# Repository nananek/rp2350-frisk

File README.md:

# pico2-compat — Pico 2 相当 + 3×USB Type-C + CH343P UART + PIO USB

Raspberry Pi Pico 2 相当の RP2350A ボードです。外形は
[nananek/serial-km-emulator](https://github.com/nananek/serial-km-emulator)
と同じ **57.6 × 31.4 mm（四隅 2 mm 45° カット）** で、旧型フリスクケース
と同じ外形寸法に収まります。

Pico 2 との違いは次のとおりです。

- Pico の micro-B を **USB Type-C** に変更（RP2350 のネイティブ USB）
- **GPIO 40 ピンを Pico と同一配置**（2.54 mm ピッチ、17.78 mm 列間）
- **BOOT と RUN の独立ボタン**
- **UART0 を CH343P 経由の Type-C** に接続（最大 6 Mbps）
- **PIO USB ホスト用 Type-C**（GP12 = D+、GP13 = D-）
- 3.3 V は AP2112K、RP2350 内蔵の 1.1 V レギュレータを使用

## 仕様

| 項目 | 内容 |
| --- | --- |
| 基板 | 57.6 × 31.4 mm、t1.6 mm、4 層、四隅 2 mm 45° カット |
| MCU | RP2350A（QFN-60、7 × 7 mm） |
| フラッシュ | W25Q32JVSSIQ（4 MB、SOIC-8 208 mil） |
| 水晶 | 12 MHz（ABM8-272-T3、3225） |
| レギュレータ | AP2112K-3.3（600 mA、VSYS 3.8〜5.5 V） |
| ネイティブ USB | Type-C、USB 2.0 Full Speed、27 Ω 直列、USBLC6 ESD |
| UART | CH343P、Type-C、UART0（GP0/GP1）、3.3 V I/O、最大 6 Mbps |
| PIO USB（ホスト） | Type-C、GP12 = D+、GP13 = D-、22 Ω 直列、CC 56 kΩ Rp、VBUS は J1 から |
| GPIO | Pico 互換 2×20（1〜20 ピン / 21〜40 ピン）、2.54 mm ピッチ、17.78 mm 列間 |
| ボタン | BOOT（QSPI_SS を 1 kΩ で GND）、RUN（1 kΩ 経由で GND） |
| デバッグ | J4 1×3 ピンヘッダ（SWCLK / GND / SWDIO、未実装） |
| 電源 | J1/J3 の VBUS を BAT54WS でダイオード OR → VSYS。J2 の VBUS は出力 |
| 実装 | 表面実装のみ（Type-C のシェル固定タブは THT） |

## Pico 互換ピン配置

基板を USB 側から見て、ピン 1 が USB 端の GP0 です。Pico と同じく、
1〜20 ピンが一方の列、21〜40 ピンがもう一方の列に並びます。
2.54 mm ピッチ、列間 17.78 mm（0.7 インチ）です。

| ピン | 名称 | ピン | 名称 | ピン | 名称 | ピン | 名称 |
| --- | --- | --- | --- | --- | --- | --- | --- |
| 1 | GP0 / UART0 TX | 11 | GP8 | 21 | GP16 | 31 | GP26 / ADC0 |
| 2 | GP1 / UART0 RX | 12 | GP9 | 22 | GP17 | 32 | GP27 / ADC1 |
| 3 | GND | 13 | GND | 23 | GND | 33 | GND |
| 4 | GP2 | 14 | GP10 | 24 | GP18 | 34 | GP28 / ADC2 |
| 5 | GP3 | 15 | GP11 | 25 | GP19 | 35 | ADC_VREF |
| 6 | GP4 | 16 | GP12 / PIO D+ | 26 | GP20 | 36 | 3V3 |
| 7 | GP5 | 17 | GP13 / PIO D- | 27 | GP21 | 37 | 3V3_EN |
| 8 | GND | 18 | GND | 28 | GND | 38 | GND |
| 9 | GP6 | 19 | GP14 | 29 | GP22 | 39 | VSYS |
| 10 | GP7 | 20 | GP15 | 30 | RUN | 40 | VBUS |

Pico 2 でヘッダに出ていない GP23〜GP25、GP29 は、本基板でもヘッダには
出していません。SWD は J4（未実装）に引き出しています。

## USB ポート

J1 / J3 は **デバイス側（CC に 5.1 kΩ の Rd）**、J2 は **ホスト側
（CC に 56 kΩ の Rp）** です。J2 の VBUS は J1 の VBUS から 0 Ω（R11）で
供給する出力です。J1 / J3 はホスト PC と C-to-C でも C-to-A でも接続でき
ます。J2 にはキーボードや USB メモリなどを接続できますが、PC や充電器は
接続しないでください。

### J1: ネイティブ USB（右小口）

RP2350 の USB_DP / USB_DM（ピン 52 / 51）を 27 Ω で J1 に接続しています。
USBLC6 で ESD 保護しています。Pico と同じく、このポートの VBUS は
ヘッダの 40 ピン（VBUS）にも出ています。

### J3: UART（下長辺・右側）

CH343P の UD+ / UD- を J3 に直結しています。CH343 のデータシートで
「UD+/UD- に直列抵抗を入れてはいけない」と指定されているため、直列抵抗は
ありません。CH343P の VIO は 3.3 V、VDD5 は VSYS（約 4.7 V）です。
UART 側は 3.3 V I/O なので、RP2350 とレベル変換なしで接続できます。

```
GP0 (TX, pin 1) ──→ CH343P RXD (pin 5)
GP1 (RX, pin 2) ←── CH343P TXD (pin 4)
```

CTS/RTS は未接続です。6 Mbps は芯線だけの短い配線で使えますが、
フロー制御が必要な用途では 2 Mbps 以下を推奨します。USB Full Speed
(12 Mbps) の実効帯域も考慮してください。

Linux では `/dev/ttyUSB0` として見えます。CH343P は WCH の VID/PID で
認識され、Linux の `ch341` ドライバで動作します。

### J2: PIO USB ホスト（下長辺・左側）

GP12 を D+、GP13 を D- にしています。22 Ω の直列抵抗と USBLC6 を実装し、
Type-C の CC は 56 kΩ の Rp（既定の USB 電流）で VBUS にプルアップして
います。このポートは **ホスト専用** で、J1（またはヘッダ 40 ピンの
VBUS）から 5 V が供給されているときだけ VBUS が出ます。Pico-PIO-USB の
ホスト機能を使う場合は
`pin_dp = 12`、`pinout = PIO_USB_PINOUT_DPDM`（D- = 13）に設定してください。
D+ / D- のプルダウンは RP2350 の内蔵抵抗を使います。

J2 は出力専用です。PC や充電器を接続しないでください。デバイス用途に
変更する場合は、R11（0 Ω）を外して D+ に 1.5 kΩ のプルアップを追加し、
CC の 56 kΩ を 5.1 kΩ の Rd に変更してください。

## 電源

J1 / J3 の VBUS を BAT54WS（D1 / D3）で OR して VSYS を作り、
AP2112K-3.3 で 3.3 V を作ります。基板は J1 / J3 のどちらからでも給電
できます。ただし J2 の VBUS は J1（ヘッダ 40 ピンの VBUS と同じ）から
取るので、J2 を使うときは J1 側に 5 V が必要です。

- VSYS: 3.8〜5.5 V（AP2112K のドロップアウトのため。USB 給電時は約 4.7 V）
- 3V3: 最大 600 mA（LDO の定格）
- RP2350 の 1.1 V は内蔵レギュレータ（VREG_VIN / VREG_LX / VREG_FB）と
  3.3 µH（L1）で生成。DVDD（ピン 6 / 23 / 39）は 1V1 に接続し、
  C11 / C12 / C30 でデカップリングします
- 3V3_EN（ヘッダ 37 ピン）は 100 kΩ で VSYS にプルアップ。GND に落とすと
  3.3 V が停止します
- VBUS（ヘッダ 40 ピン）は J1 の VBUS に直結
- J2 の VBUS は J1 の VBUS（ヘッダ 40 ピンと同じ）から R11（0 Ω）で供給
- VSYS（ヘッダ 39 ピン）はダイオード OR 後の共通 5 V

Pico の 3V3 ピン（36）は本基板では LDO 出力です。外部から 3V3 を
逆駆動しないでください。VSYS から給電する場合も、LDO の入力範囲
（3.8 V 以上）を守ってください。バッテリー直結（3.7 V 以下）では
3.3 V が低下します。

## BOOT / RUN

- **BOOT**: QSPI_SS とフラッシュ CS の間の 0 Ω（R14）の前から 1 kΩ（R12）で
  ボタンに引き出しています。BOOT を押したままリセットすると、RP2350 の
  USB ブートローダー（BOOTSEL）に入ります。
- **RUN**: RUN ピンを 1 kΩ（R13）経由で GND に落とします。

BOOT と RUN は独立したタクトスイッチ（TS-1187A、5.1 × 5.1 mm）です。

## 基板外形とケース

外形は serial-km-emulator と同一の 57.6 × 31.4 mm、四隅 2 mm 45° カット
です。配線とグラウンドの都合で 4 層にしています。旧型フリスクケースの内寸には収まりますが、コネクタの位置が違うため
ケースの開口を変更してください。

- J2 / J3（PIO USB / UART）: 下長辺に 2 個。開口は約 30 × 5 mm
- J1（ネイティブ USB）: 右小口に 1 個。開口は約 10 × 5 mm
- BOOT / RUN: 基板の表側、左右の端。ケースに穴を開けるか、蓋を外して押します

コネクタの口は基板端から約 1.5 mm 外に出ます。USB-C プラグの
オーバーモールドがケースに当たる場合は、開口の外側を面取りしてください。

## 部品表（JLCPCB）

`fab/bom_jlcpcb.csv` が JLCPCB 用 BOM、`fab/cpl_jlcpcb.csv` が CPL です。
主な部品は次のとおりです（2026-11 時点の JLCPCB 在庫確認済み）。

| 記号 | 値 | パッケージ | LCSC | 備考 |
| --- | --- | --- | --- | --- |
| U1 | RP2350A | QFN-60 7×7 | C42411118 | 拡張部品 |
| U2 | W25Q32JVSSIQ | SOIC-8 208 mil | C179173 | 4 MB |
| U3 | CH343P | QFN-16 3×3 | C2846043 | 6 Mbps、水晶不要 |
| U4 | AP2112K-3.3 | SOT-23-5 | C51118 | 600 mA LDO |
| J1〜J3 | TYPE-C-31-M-12 | USB-C 16P | C165948 | HRO |
| D1, D3 | BAT54WS | SOD-323 | C22629 | VBUS OR |
| D4〜D6 | USBLC6-2SC6 | SOT-23-6 | C7519 | ESD |
| Y1 | ABM8-272-T3 | 3225 4 pin | C20625731 | 12 MHz |
| L1 | 3.3 µH | 2016 | C42411119 | RP2350 1.1 V 用 |
| SW1, SW2 | TS-1187A-B-A-B | 5.1×5.1 mm | C318884 | BOOT / RUN |
| R1, R2, R5, R6 | 5.1 kΩ | 0603 | C23186 | CC（デバイス） |
| R3, R4 | 56 kΩ | 0603 | C23206 | CC（ホスト Rp） |
| R7, R8 | 27 Ω | 0603 | C25190 | ネイティブ USB |
| R9, R10 | 22 Ω | 0603 | C23345 | PIO USB |
| R11 | 0 Ω | 0603 | C21189 | PIO VBUS（J1 VBUS → J2） |
| R12, R13, R18〜R20 | 1 kΩ | 0603 | C21190 | BOOT/RUN/LED/水晶 |
| R14 | 0 Ω | 0603 | C21189 | QSPI_SS |
| R15 | 33 Ω | 0603 | C23140 | VREG_AVDD |
| R16 | 200 Ω | 0603 | C8218 | ADC_VREF |
| R17 | 100 kΩ | 0603 | C14675 | 3V3_EN |
| C1〜C3, C7, C9 | 10 µF | 0805 | C15850 | VBUS / VSYS / 3V3 |
| C11, C13, C30 | 4.7 µF | 0805 | C1779 | 1V1（C30 はピン 23 付近） / VREG_AVDD |
| C4〜C6, C8, C10, C12, C14〜C29 | 100 nF | 0603 | C14663 | デカップリング |
| C25, C26 | 15 pF | 0603 | C1644 | 水晶 |
| LED1, LED2 | KT-0603R | 0603 | C2286 | PWR / UART ACT |

J5A / J5B（Pico ヘッダ）と J4（SWD）は **未実装** です。BOM / CPL には
入りません。

## JLCPCB での発注

基板:

- 4 層、57.6 × 31.4 mm、t1.6 mm、FR-4、HASL、1 oz
- 内層: In1 = GND ベタ、In2 = 3V3 ベタ
- 最小配線幅/間隔 0.10/0.15 mm、ビア 0.5/0.3 mm
- 仕上げはお好みで（HASL / 鉛フリー HASL / ENIG）

実装:

- 表面のみ
- アップロードするファイル:
  - ガーバー: `fab/pico2-compat-gerbers.zip`
  - BOM: `fab/bom_jlcpcb.csv`
  - CPL: `fab/cpl_jlcpcb.csv`
- Type-C のシェル固定タブは THT 形状ですが、JLCPCB の SMT 実装部品として
  登録されています（C165948）。
- CPL の回転は KiCad → JLC の一般的な補正を入れてあります。必ず
  JLCPCB の実装プレビューで IC のピン 1 と Type-C の向きを確認してください。
- R3 / R4 の VBUS 側は 0603 パッド内のビア（0.5/0.3 mm）で VBUS_PIO に
  接続しています。量産時は via-in-pad のビア埋めを検討してください。
- QFN（RP2350A / CH343P）は拡張部品です。手半田する場合は、センターパッド
  へのプリフォーム半田またはホットエアを使ってください。

## 再生成

KiCad 10 の `kicad-cli` と Python の `pcbnew` を使います。Docker がある場合は
`scripts/kicad.sh` 経由で実行できます。

```sh
# 回路図と配置（配線は消えるので注意）
./scripts/kicad.sh python3 scripts/gen_sch.py
./scripts/kicad.sh python3 scripts/gen_pcb.py

# ガーバー、ドリル、BOM、CPL、PDF
./scripts/kicad.sh ./scripts/export_fab.sh
```

`pico2-compat.kicad_pcb` は `scripts/gen_pcb.py` が配置と外形を作り、
`scripts/route.sh` の Freerouting で配線を入れています。配置を変えた場合は
配線をやり直してください。`scripts/finish_pcb.py` が GND ベタを追加して
フィルし、最終基板を作ります。

```sh
./scripts/route.sh          # DSN 書き出し → Freerouting → SES 取り込み
./scripts/kicad.sh python3 scripts/finish_pcb.py
```

Freerouting は [`freerouting/freerouting`](https://github.com/freerouting/freerouting)
の CLI を使います。Java 21 以上が必要です。

## 検証

GitHub Actions（`.github/workflows/ci.yml`）で次を実行します。

- ERC: 0 件
- DRC: エラー 0 件（`--severity-error`）
- ガーバー、ドリル、BOM、CPL、PDF の生成
- 生成物のアップロード

シルクの文字高やシルクとパッドのクリアランスは警告として残る場合があります。
製造には影響しませんが、気になる場合はシルクを調整してください。

## 制限事項

- PIO USB（J2）はホスト専用です。VBUS は J1（またはヘッダ 40 ピン）から
  供給されるため、J1 側に 5 V がないと J2 のデバイスは動作しません。J2 から
  基板へ給電することはできません。
- CH343P の CTS/RTS は未接続です。
- 3.3 V は LDO のため、VSYS が 3.8 V を下回ると 3.3 V が低下します。
- Pico 2 の buck-boost のような広い VSYS 入力範囲ではありません。
- GP23〜GP25、GP29 はヘッダに出ていません（Pico と同じ）。
- SWD は J4 に引き出していますが、実装はしていません。
- ネイティブ USB の VBUS（ヘッダ 40 ピン）と VSYS（39 ピン）は Pico と
  同じ向きですが、3V3（36 ピン）を外部から逆駆動しないでください。

## ファイル構成

```
pico2-compat.kicad_pro / .kicad_sch / .kicad_pcb / .kicad_dru
lib/pico2.kicad_sym          回路図シンボル
lib/PICO2.pretty/            フットプリント
scripts/design.py            部品・ネットの単一ソース
scripts/gen_sch.py           回路図生成
scripts/gen_pcb.py           配置・外形生成
scripts/route.sh             Freerouting による配線
scripts/finish_pcb.py        GND ベタ追加・フィル
scripts/export_fab.sh        ガーバー/BOM/CPL/PDF 生成
scripts/make_jlc_files.py    JLCPCB BOM/CPL 変換
.github/workflows/ci.yml     CI
fab/                         発注用ファイル（生成物）
docs/                        基板画像・回路図 PDF
```

## ライセンス

MIT。基板の製造・実装は自己責任で行ってください。特に Type-C のシェル
固定タブ、USB の差し込み方向、ケースの開口寸法は、発注前に各自の環境で
確認してください。

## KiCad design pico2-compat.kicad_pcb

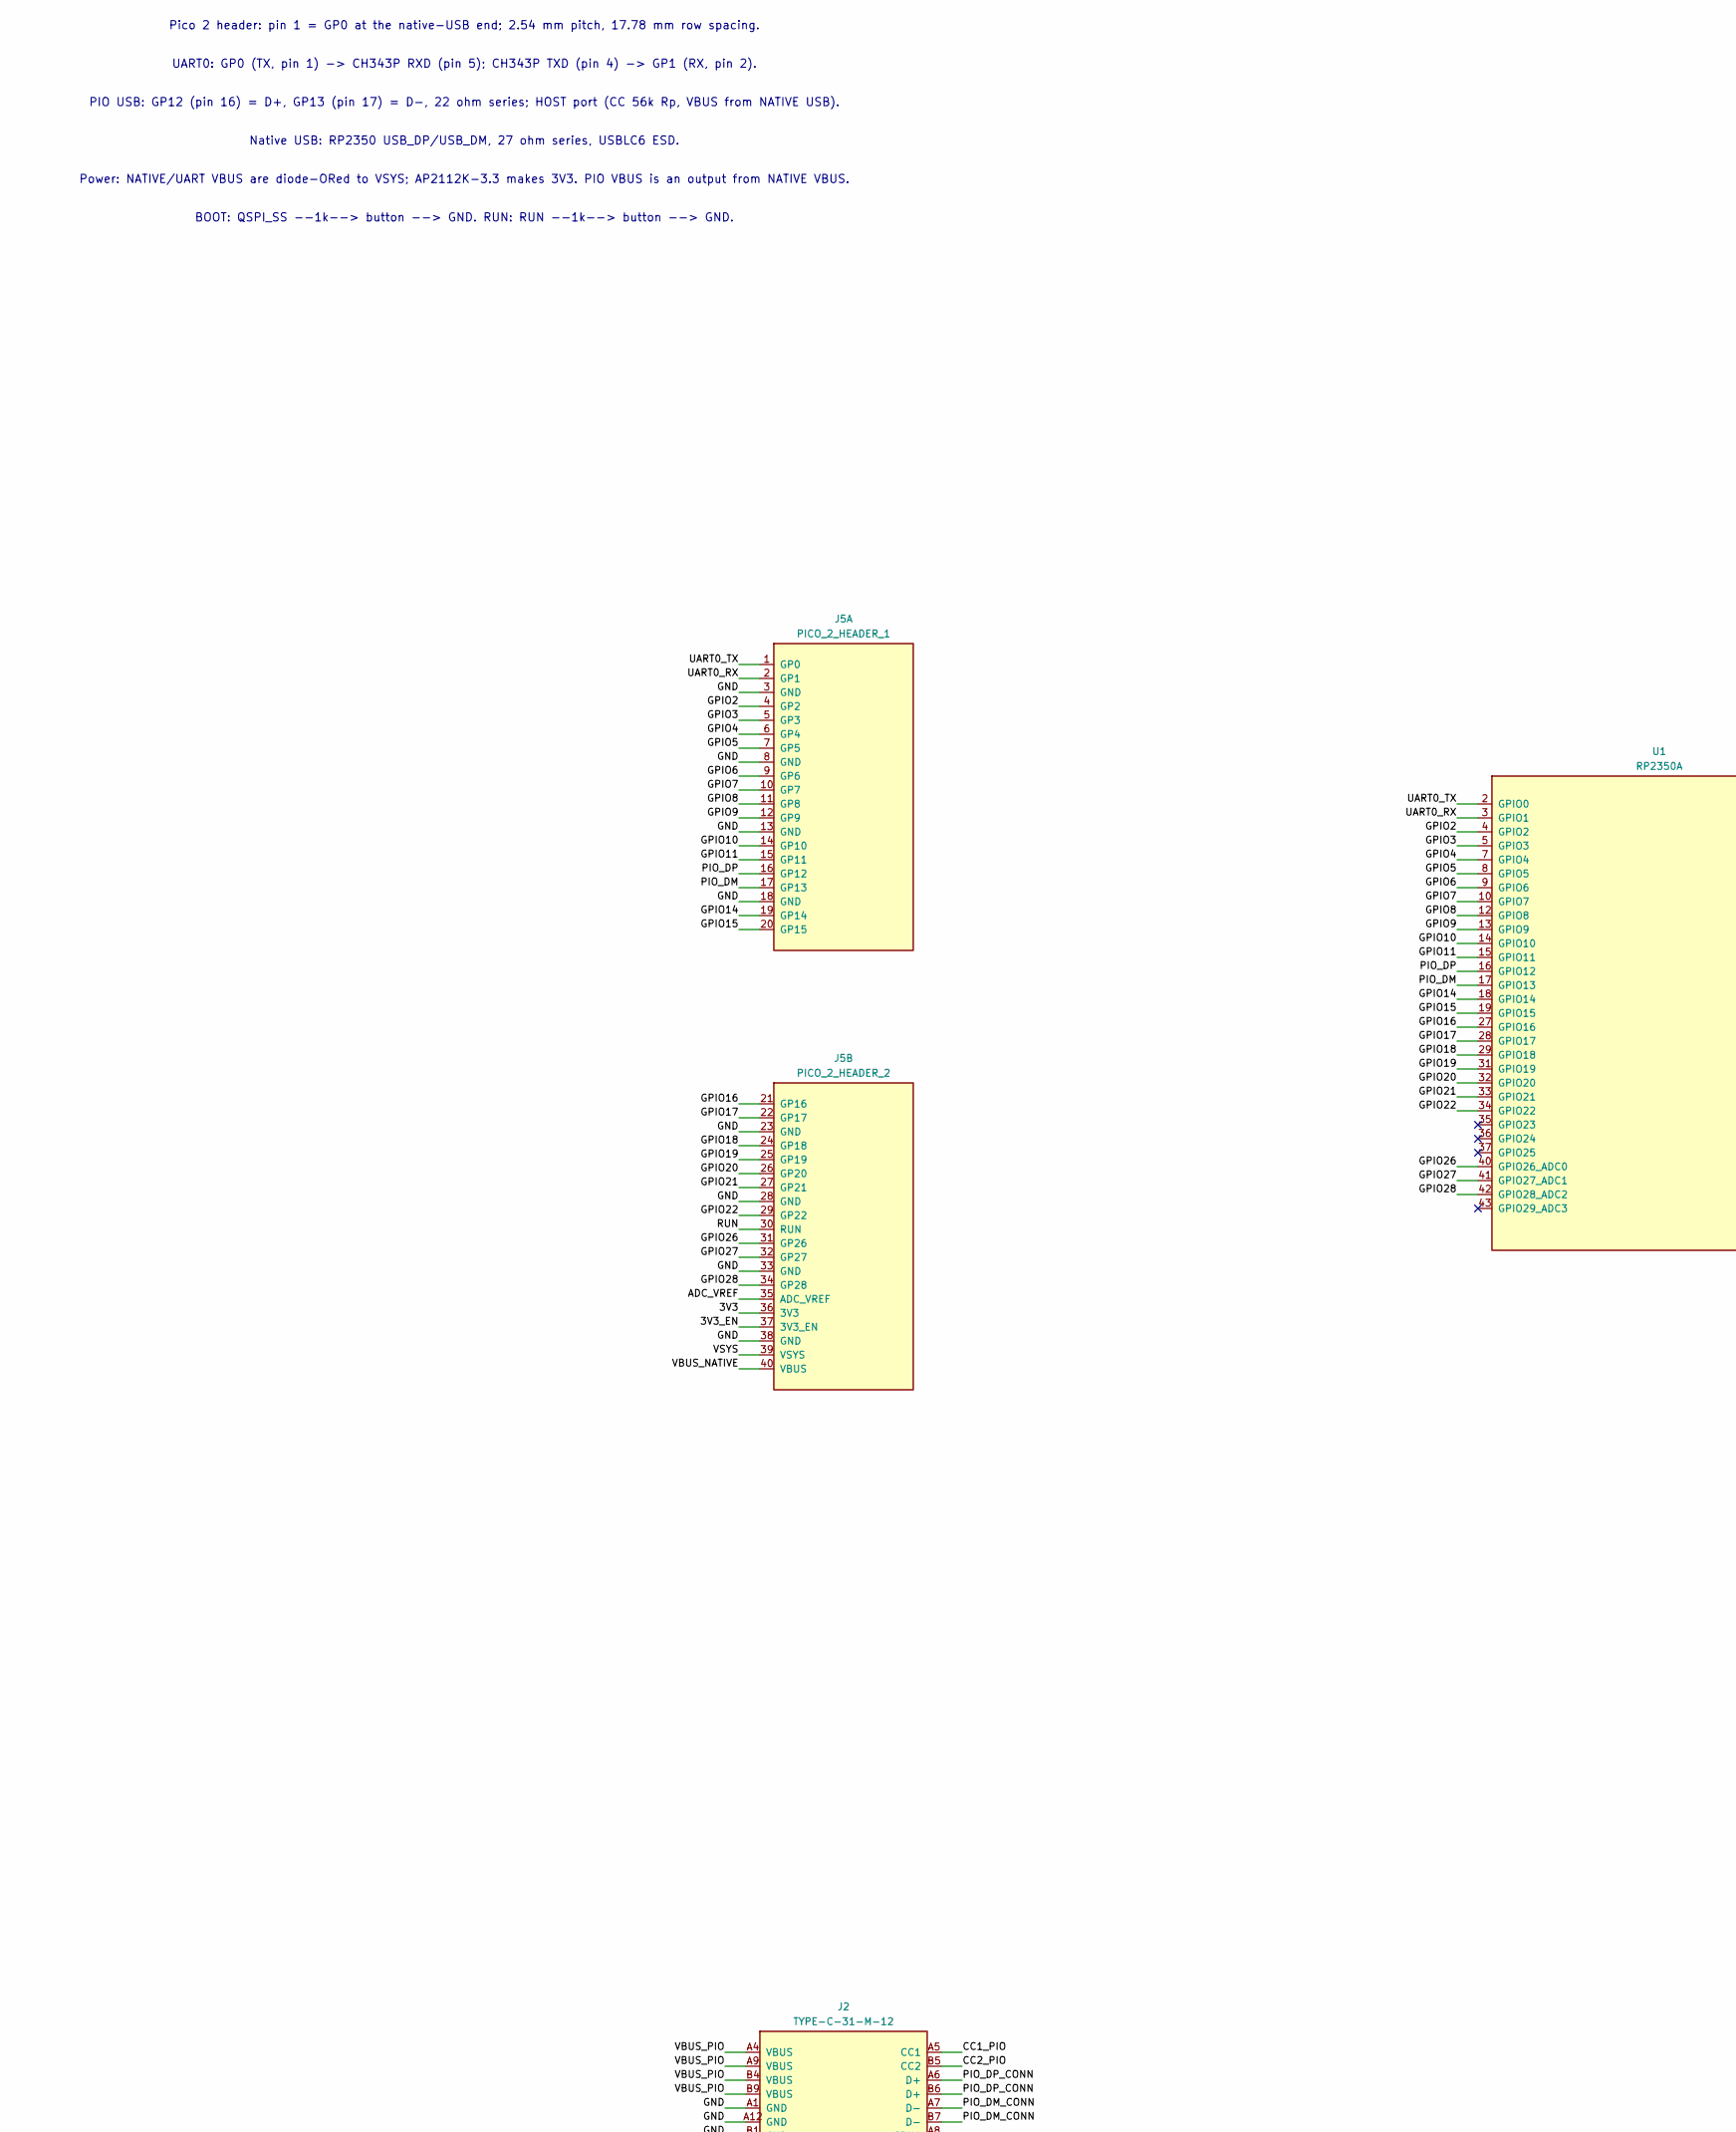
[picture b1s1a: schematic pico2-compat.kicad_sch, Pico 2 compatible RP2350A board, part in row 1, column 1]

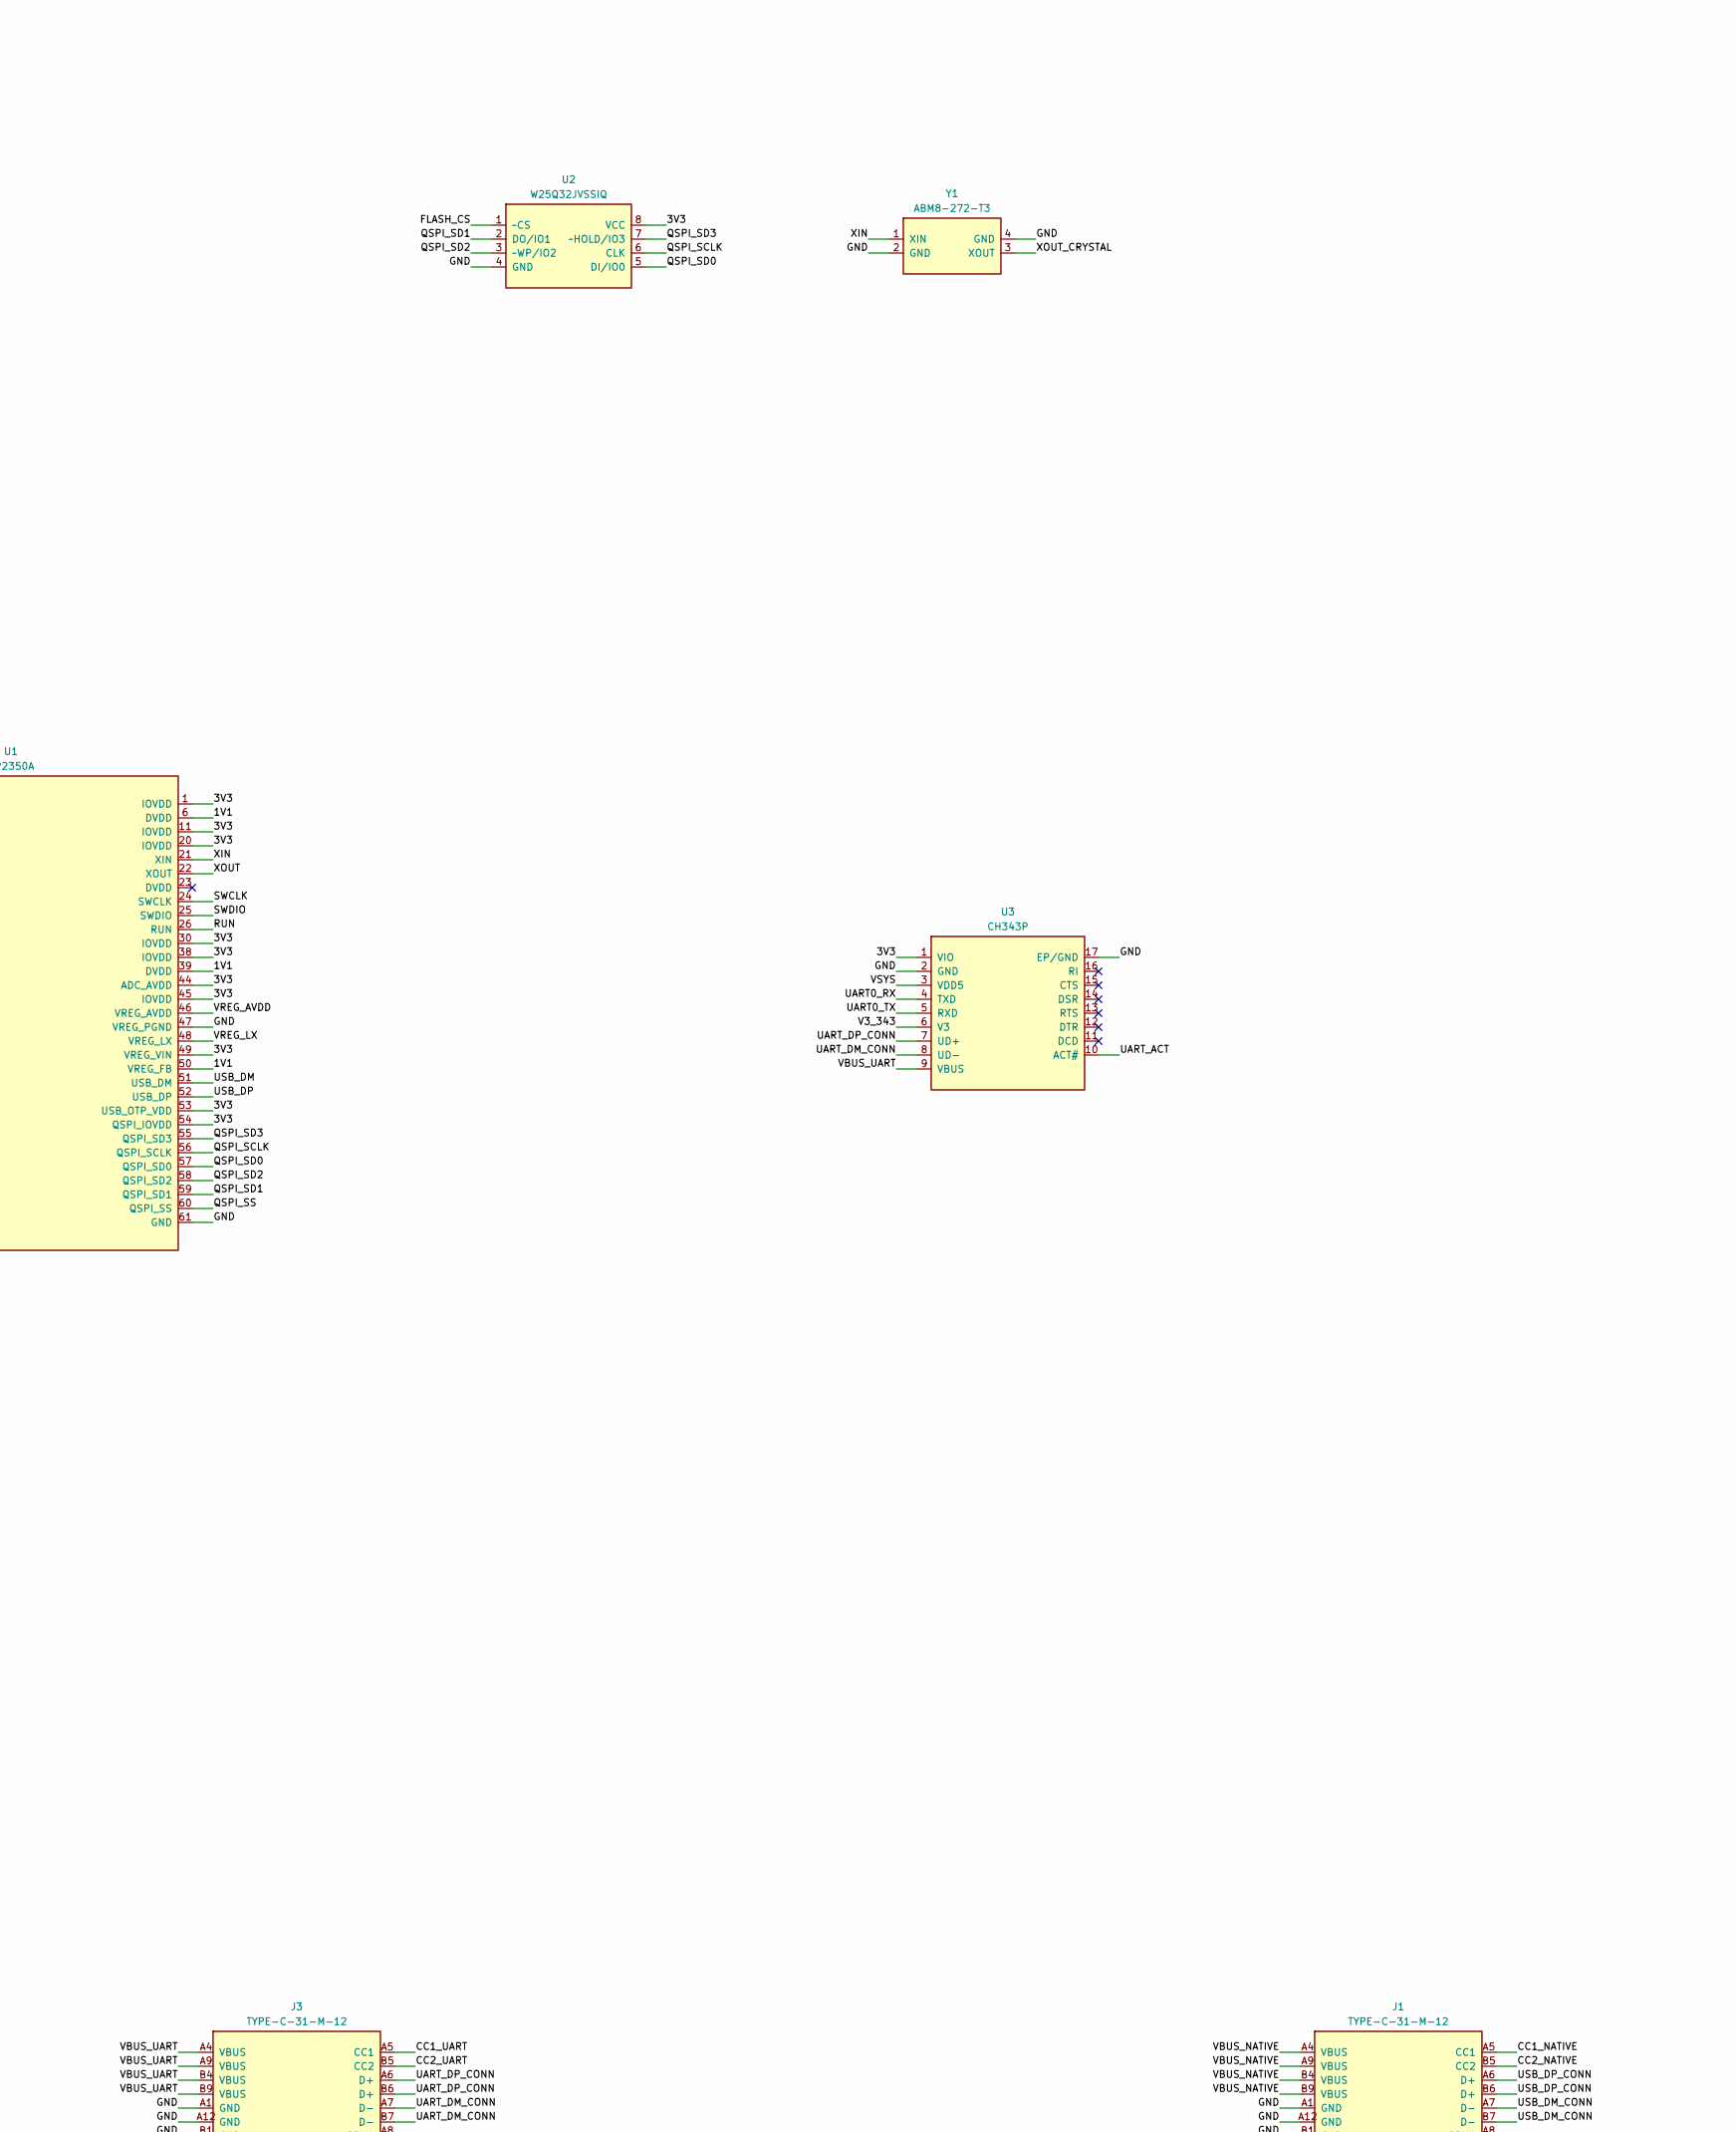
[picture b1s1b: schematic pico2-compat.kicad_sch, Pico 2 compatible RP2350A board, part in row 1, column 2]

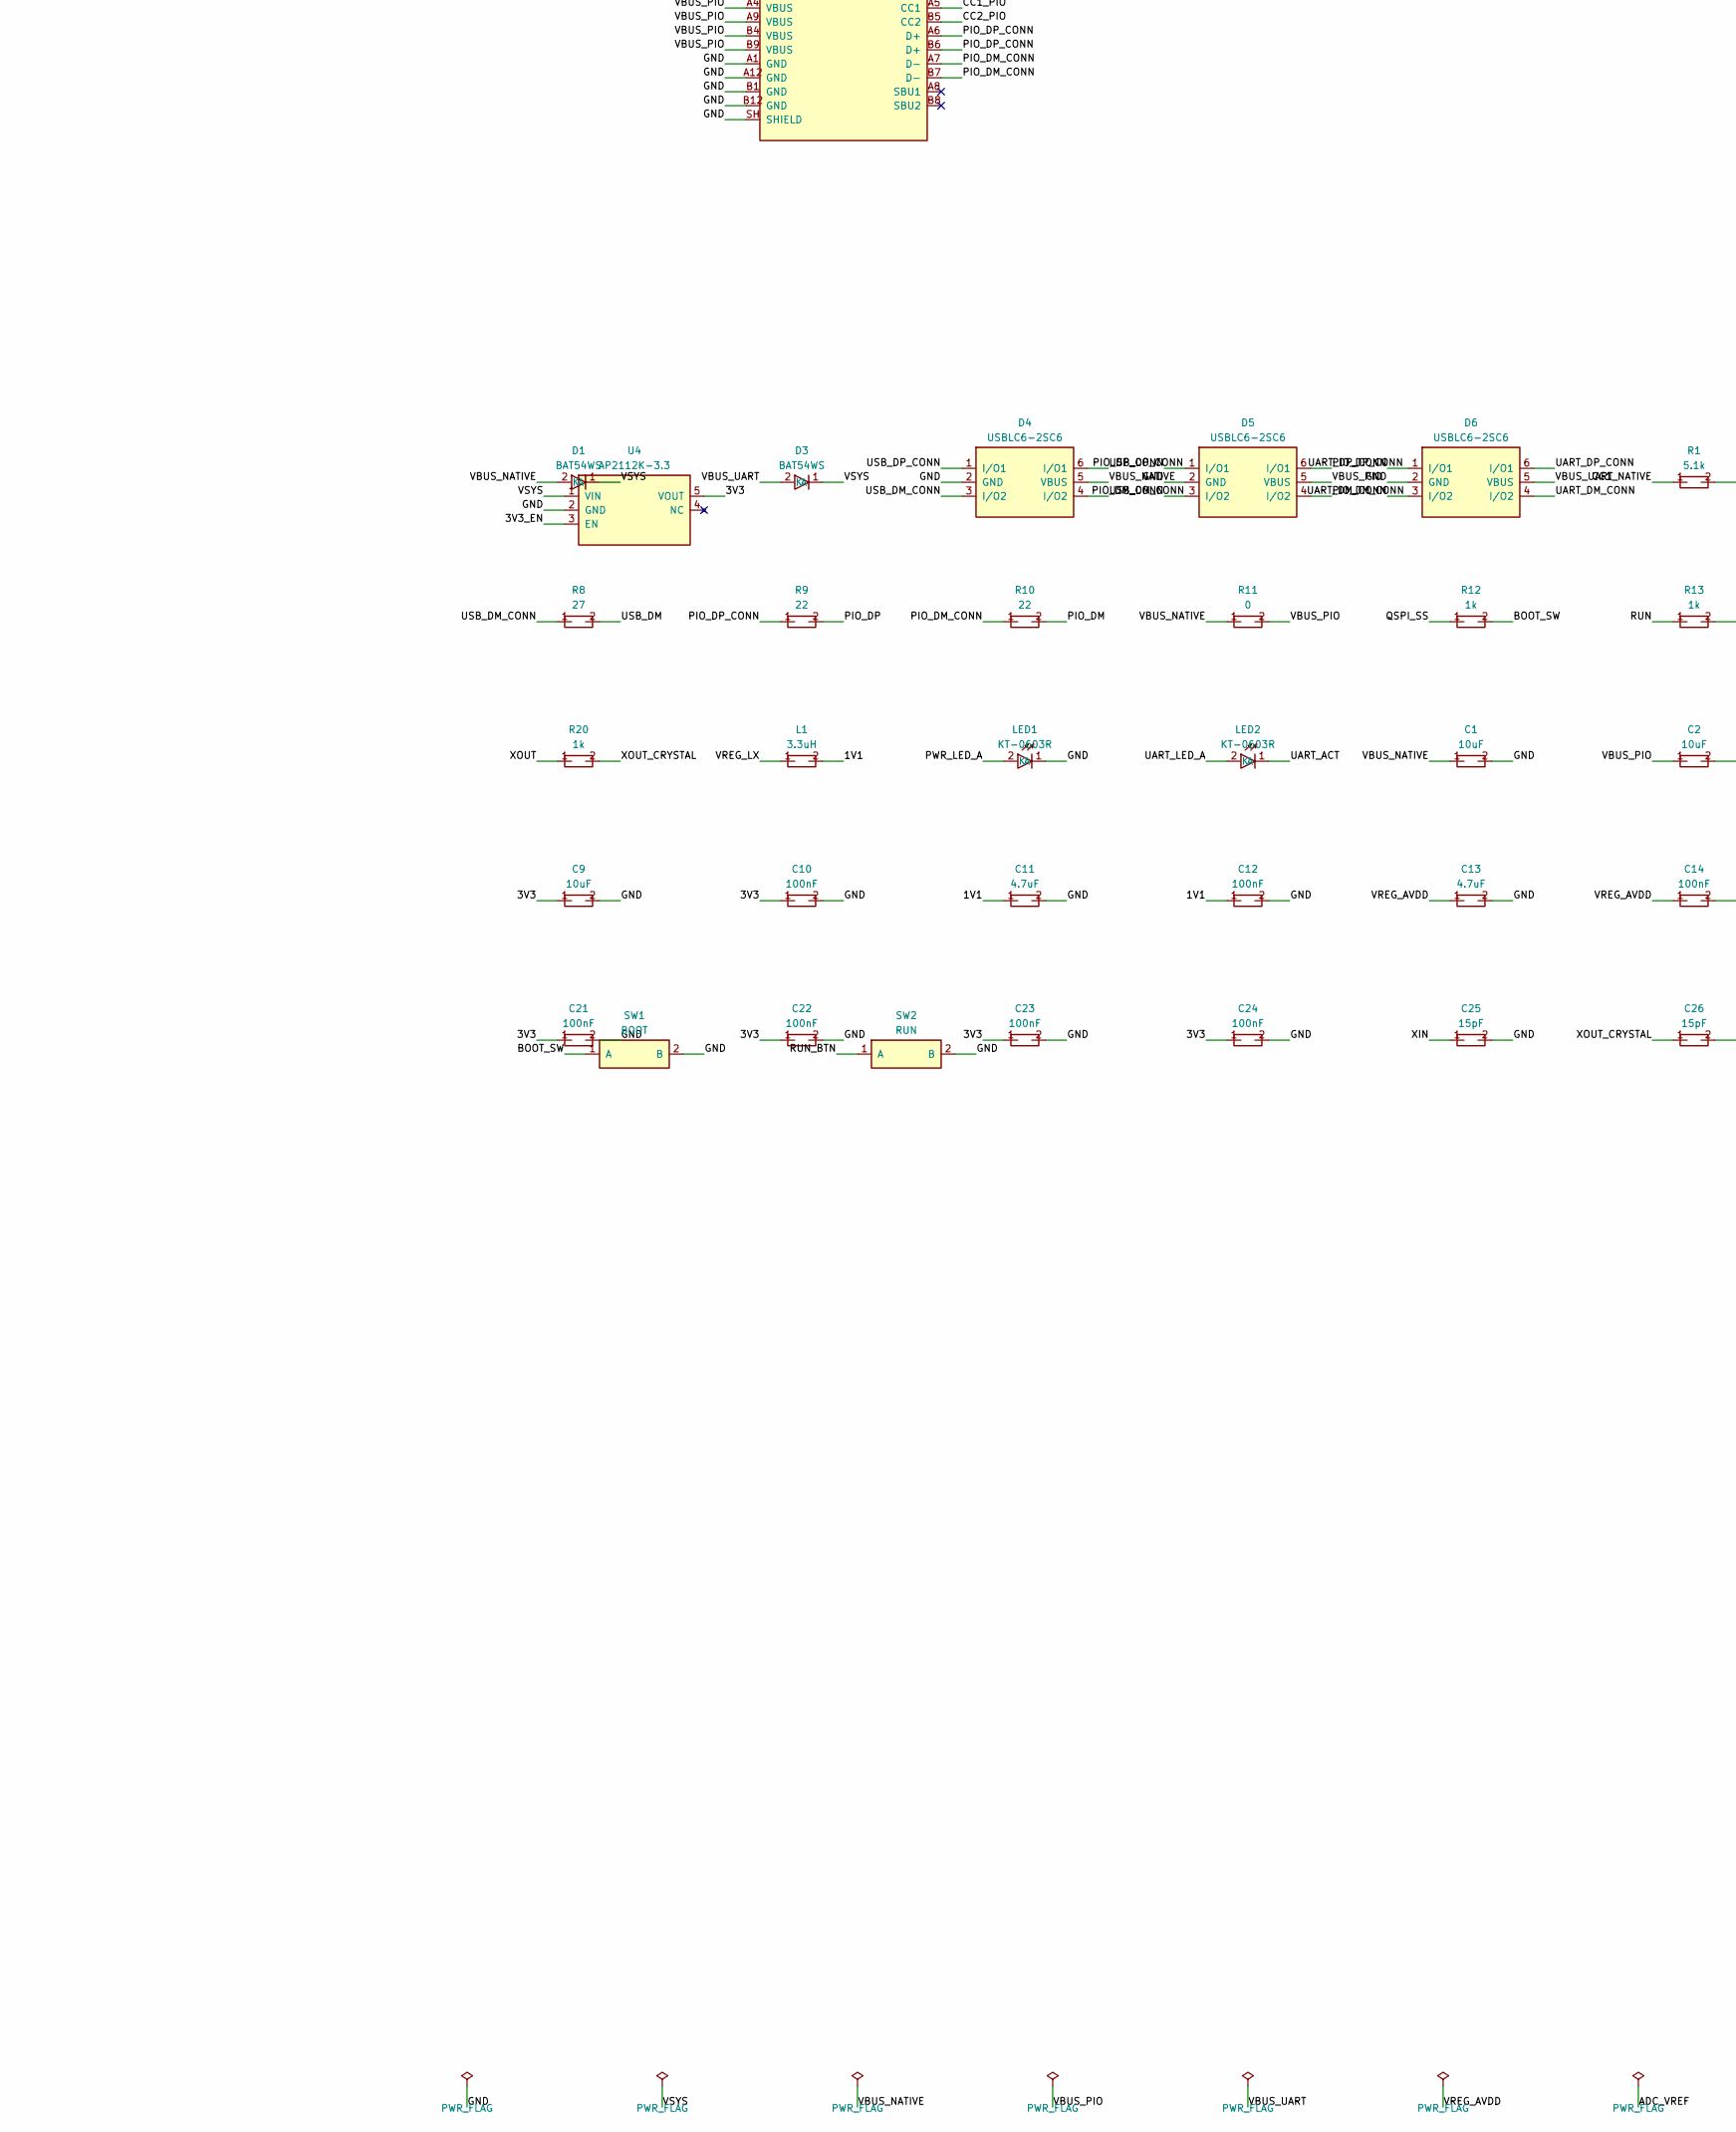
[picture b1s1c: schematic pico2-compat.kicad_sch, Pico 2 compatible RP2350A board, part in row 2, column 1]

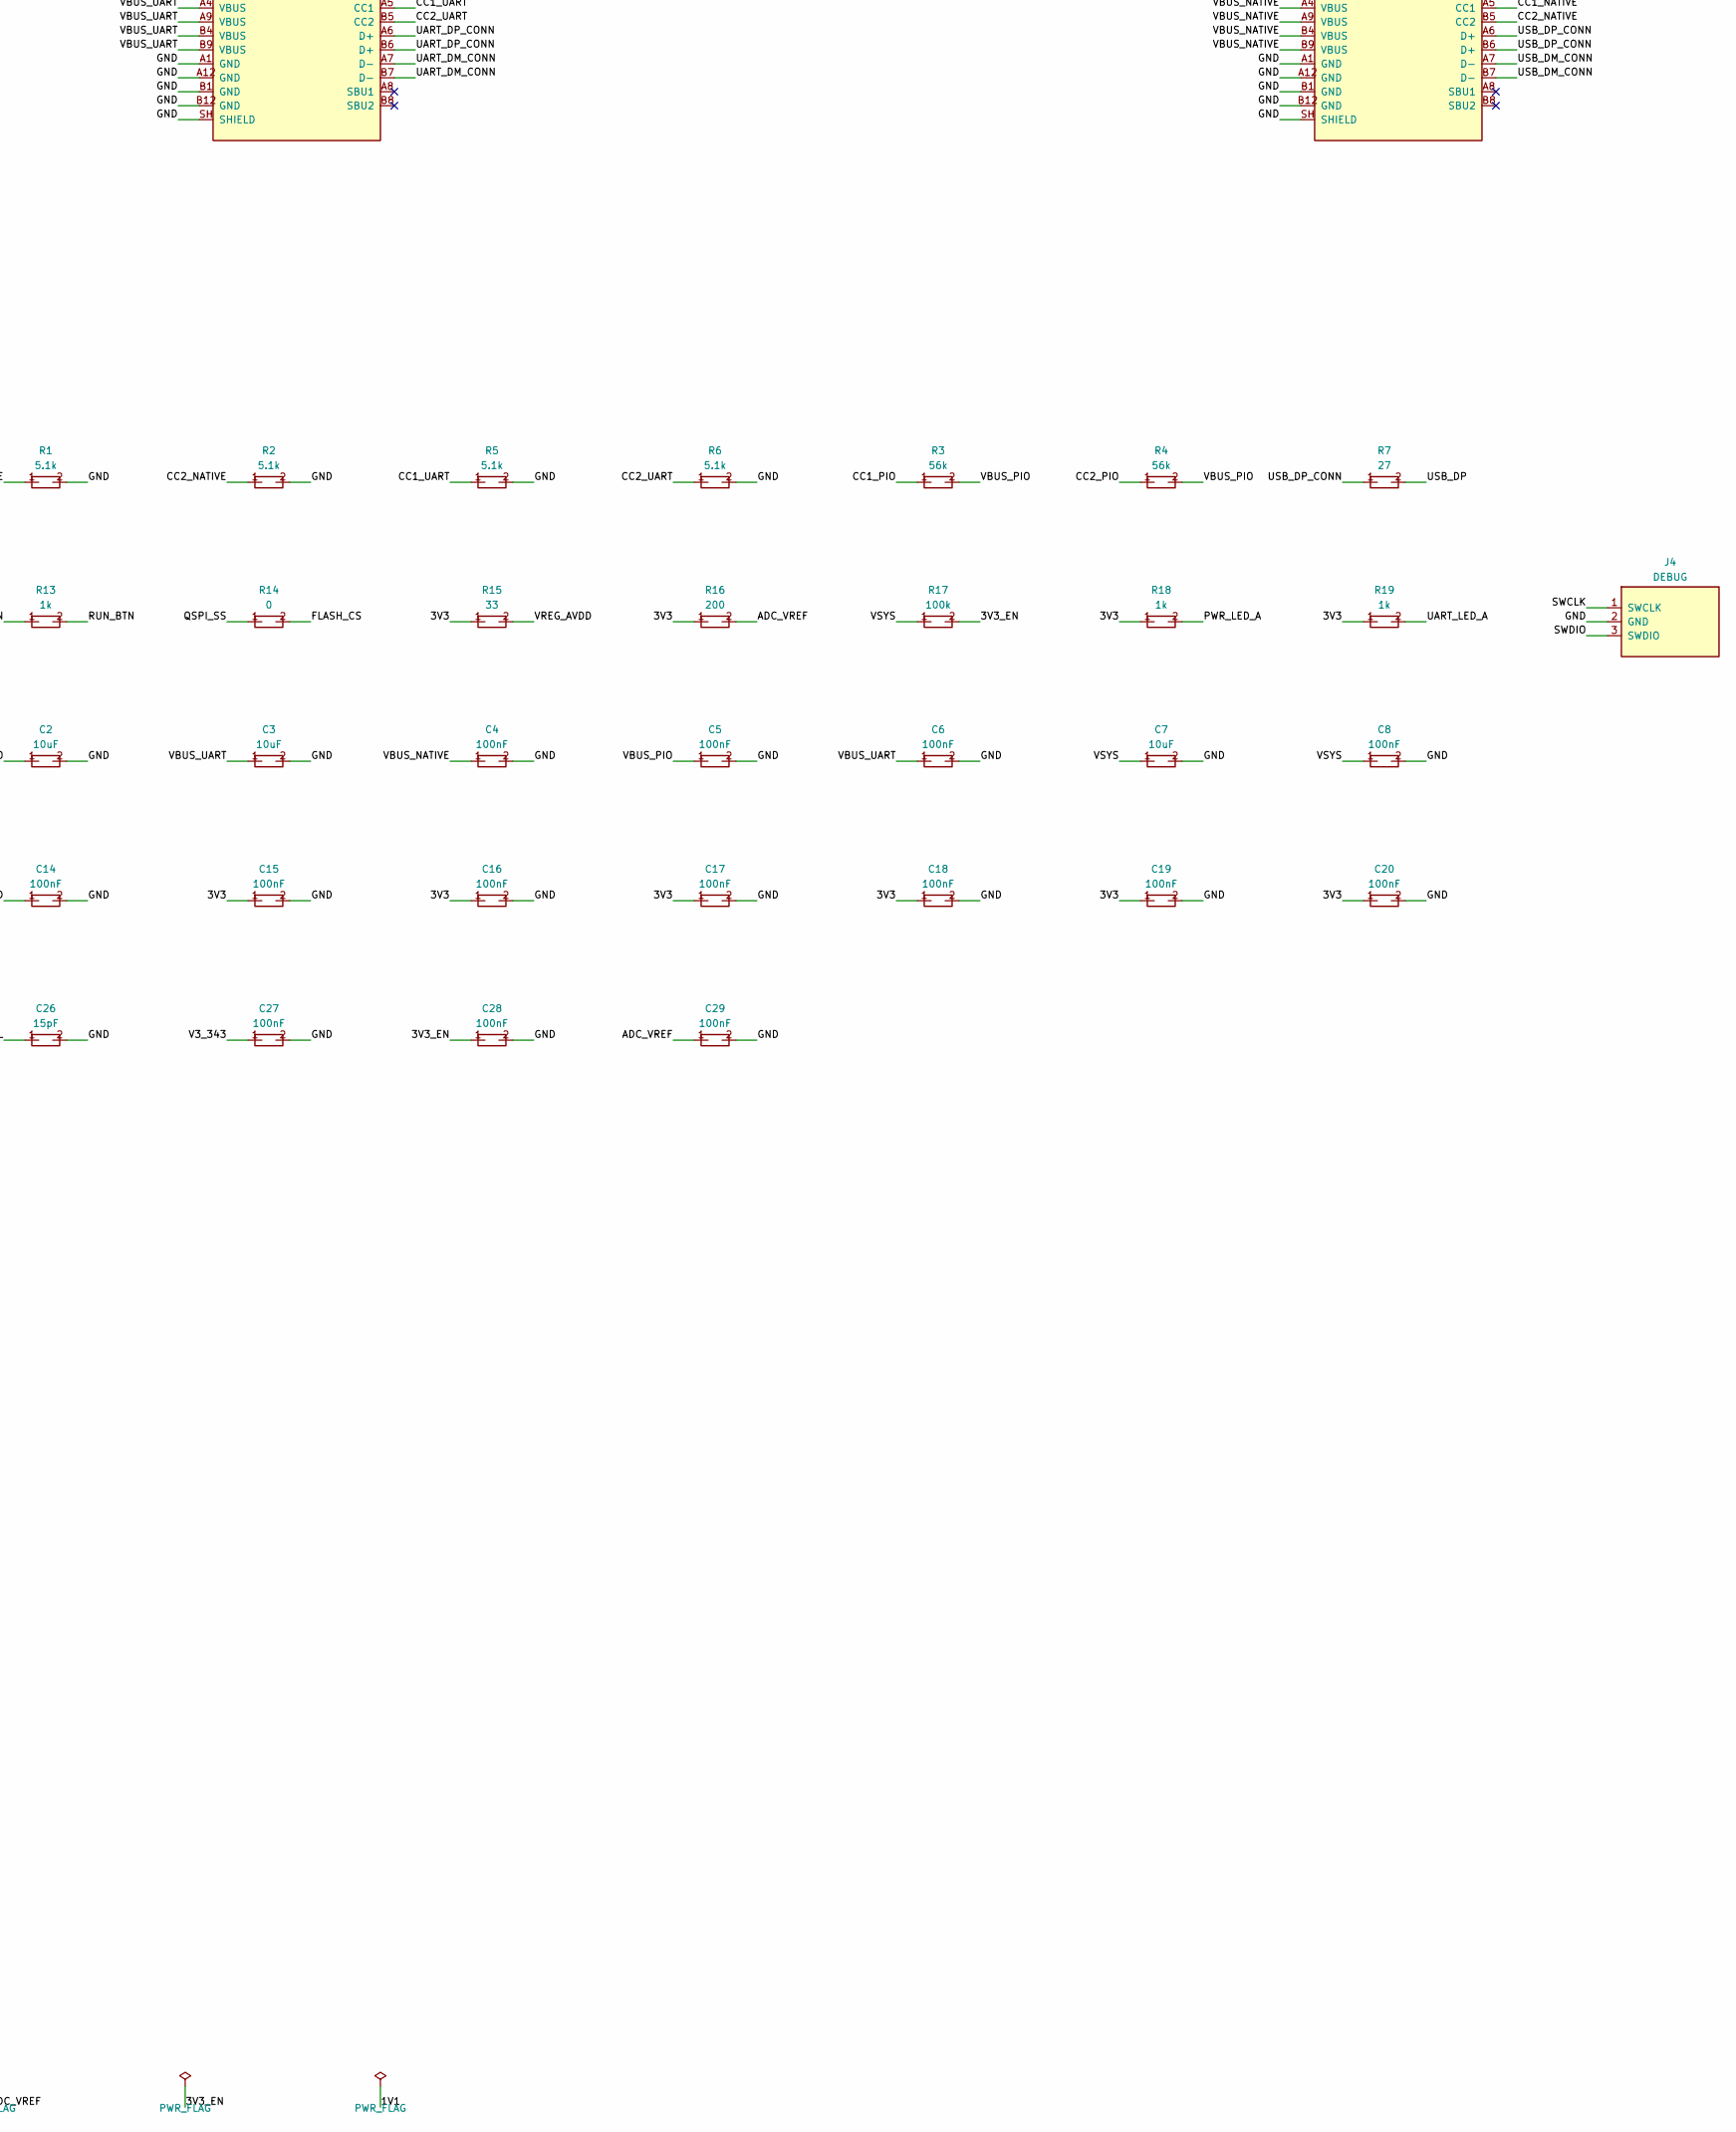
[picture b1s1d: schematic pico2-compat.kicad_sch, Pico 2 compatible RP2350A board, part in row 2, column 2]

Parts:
C1, C2, C3, C7, C9: 10uF; C_0805_2012Metric; LCSC C15850
C4, C5, C6, C8, C10, C12, C14, C15, C16, C17, C18, C19, C20, C21, C22, C23, C24, C27, C28, C29: 100nF; C_0603_1608Metric; LCSC C14663
C11, C13: 4.7uF; C_0805_2012Metric; LCSC C1779
C25, C26: 15pF; C_0603_1608Metric; LCSC C1644
D1, D3: BAT54WS; D_SOD-323; LCSC C22629
D4, D5, D6: USBLC6-2SC6; SOT-23-6; LCSC C7519
J1, J2, J3: TYPE-C-31-M-12; USB_C_Receptacle_HRO_TYPE-C-31-M-12; LCSC C165948
J4: DEBUG; PinHeader_1x03_P2.54mm_Vertical
J5A: PICO_2_HEADER_1; PinHeader_1x20_Pico_Top
J5B: PICO_2_HEADER_2; PinHeader_1x20_Pico_Bottom
L1: 3.3uH; L_pol_2016; LCSC C42411119
LED1, LED2: KT-0603R; LED_0603_1608Metric; LCSC C2286
R1, R2, R5, R6: 5.1k; R_0603_1608Metric; LCSC C23186
R3, R4: 56k; R_0603_1608Metric; LCSC C23206
R7, R8: 27; R_0603_1608Metric; LCSC C25190
R9, R10: 22; R_0603_1608Metric; LCSC C23345
R11, R14: 0; R_0603_1608Metric; LCSC C21189
R12, R13, R18, R19, R20: 1k; R_0603_1608Metric; LCSC C21190
R15: 33; R_0603_1608Metric; LCSC C23140
R16: 200; R_0603_1608Metric; LCSC C8218
R17: 100k; R_0603_1608Metric; LCSC C14675
SW1: BOOT; SW_Push_1P1T_XKB_TS-1187A; LCSC C318884
SW2: RUN; SW_Push_1P1T_XKB_TS-1187A; LCSC C318884
U1: RP2350A; RP2350-QFN-60-1EP_7x7_P0.4mm_EP3.4x3.4mm_ThermalVias; LCSC C42411118
U2: W25Q32JVSSIQ; SOIC-8_5.3x5.3mm_P1.27mm; LCSC C179173
U3: CH343P; QFN-16-1EP_3x3mm_P0.5mm_EP1.7x1.7mm; LCSC C2846043
U4: AP2112K-3.3; SOT-23-5; LCSC C51118
Y1: ABM8-272-T3; Crystal_SMD_3225-4Pin_3.2x2.5mm; LCSC C20625731

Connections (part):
1V1: C11.1, C12.1, L1.2, U1.6 (DVDD), U1.23 (DVDD), U1.39 (DVDD), U1.50 (VREG_FB); also elsewhere on the board
3V3: C9.1, C10.1, C15.1, C16.1, C17.1, C18.1, C19.1, C20.1, C21.1, C22.1, C23.1, C24.1, J5B.36 (3V3), R15.1, R16.1, R18.1, R19.1, U1.1 (IOVDD), U1.11 (IOVDD), U1.20 (IOVDD), U1.30 (IOVDD), U1.38 (IOVDD), U1.44 (ADC_AVDD), U1.45 (IOVDD), U1.49 (VREG_VIN), U1.53 (USB_OTP_VDD), U1.54 (QSPI_IOVDD), U2.8 (VCC), U3.1 (VIO), U4.5 (VOUT)
3V3_EN: C28.1, J5B.37 (3V3_EN), R17.2, U4.3 (EN)
ADC_VREF: C29.1, J5B.35 (ADC_VREF), R16.2
BOOT_SW: R12.2, SW1.1 (A)
CC1_NATIVE: J1.A5 (CC1), R1.1
CC1_PIO: J2.A5 (CC1), R3.1
CC1_UART: J3.A5 (CC1), R5.1
CC2_NATIVE: J1.B5 (CC2), R2.1
CC2_PIO: J2.B5 (CC2), R4.1
CC2_UART: J3.B5 (CC2), R6.1
FLASH_CS: R14.2, U2.1 (~CS)
GND: C1.2, C2.2, C3.2, C4.2, C5.2, C6.2, C7.2, C8.2, C9.2, C10.2, C11.2, C12.2, C13.2, C14.2, C15.2, C16.2, C17.2, C18.2, C19.2, C20.2, C21.2, C22.2, C23.2, C24.2, C25.2, C26.2, C27.2, C28.2, C29.2, D4.2 (GND), D5.2 (GND), D6.2 (GND), J1.A1 (GND), J1.A12 (GND), J1.B1 (GND), J1.B12 (GND), J1.SH (SHIELD), J2.A1 (GND), J2.A12 (GND), J2.B1 (GND), J2.B12 (GND), J2.SH (SHIELD), J3.A1 (GND), J3.A12 (GND), J3.B1 (GND), J3.B12 (GND), J3.SH (SHIELD), J4.2 (GND), J5A.3 (GND), J5A.8 (GND), J5A.13 (GND), J5A.18 (GND), J5B.23 (GND), J5B.28 (GND), J5B.33 (GND), J5B.38 (GND), LED1.1 (K), R1.2, R2.2, R5.2, R6.2, SW1.2 (B), SW2.2 (B), U1.47 (VREG_PGND), U1.61 (GND), U2.4 (GND), U3.2 (GND), U3.17 (EP/GND), U4.2 (GND), Y1.2 (GND), Y1.4 (GND); also elsewhere on the board
GPIO2: J5A.4 (GP2), U1.4 (GPIO2)
GPIO3: J5A.5 (GP3), U1.5 (GPIO3)
GPIO4: J5A.6 (GP4), U1.7 (GPIO4)
GPIO5: J5A.7 (GP5), U1.8 (GPIO5)
GPIO6: J5A.9 (GP6), U1.9 (GPIO6)
GPIO7: J5A.10 (GP7), U1.10 (GPIO7)
GPIO8: J5A.11 (GP8), U1.12 (GPIO8)
GPIO9: J5A.12 (GP9), U1.13 (GPIO9)
GPIO10: J5A.14 (GP10), U1.14 (GPIO10)
GPIO11: J5A.15 (GP11), U1.15 (GPIO11)
GPIO14: J5A.19 (GP14), U1.18 (GPIO14)
GPIO15: J5A.20 (GP15), U1.19 (GPIO15)
GPIO16: J5B.21 (GP16), U1.27 (GPIO16)
GPIO17: J5B.22 (GP17), U1.28 (GPIO17)
GPIO18: J5B.24 (GP18), U1.29 (GPIO18)
GPIO19: J5B.25 (GP19), U1.31 (GPIO19)
GPIO20: J5B.26 (GP20), U1.32 (GPIO20)
GPIO21: J5B.27 (GP21), U1.33 (GPIO21)
GPIO22: J5B.29 (GP22), U1.34 (GPIO22)
GPIO26: J5B.31 (GP26), U1.40 (GPIO26_ADC0)
GPIO27: J5B.32 (GP27), U1.41 (GPIO27_ADC1)
GPIO28: J5B.34 (GP28), U1.42 (GPIO28_ADC2)
PIO_DM: J5A.17 (GP13), R10.2, U1.17 (GPIO13)
PIO_DM_CONN: D5.3 (I/O2), D5.4 (I/O2), J2.A7 (D-), J2.B7 (D-), R10.1
PIO_DP: J5A.16 (GP12), R9.2, U1.16 (GPIO12)
PIO_DP_CONN: D5.1 (I/O1), D5.6 (I/O1), J2.A6 (D+), J2.B6 (D+), R9.1
PWR_LED_A: LED1.2 (A), R18.2
QSPI_SCLK: U1.56 (QSPI_SCLK), U2.6 (CLK)
QSPI_SD0: U1.57 (QSPI_SD0), U2.5 (DI/IO0)
QSPI_SD1: U1.59 (QSPI_SD1), U2.2 (DO/IO1)
QSPI_SD2: U1.58 (QSPI_SD2), U2.3 (~WP/IO2)
QSPI_SD3: U1.55 (QSPI_SD3), U2.7 (~HOLD/IO3)
QSPI_SS: R12.1, R14.1, U1.60 (QSPI_SS)
RUN: J5B.30 (RUN), R13.1, U1.26 (RUN)
RUN_BTN: R13.2, SW2.1 (A)
SWCLK: J4.1 (SWCLK), U1.24 (SWCLK)
SWDIO: J4.3 (SWDIO), U1.25 (SWDIO)
UART0_RX: J5A.2 (GP1), U1.3 (GPIO1), U3.4 (TXD)
UART0_TX: J5A.1 (GP0), U1.2 (GPIO0), U3.5 (RXD)
UART_ACT: LED2.1 (K), U3.10 (ACT#)
UART_DM_CONN: D6.3 (I/O2), D6.4 (I/O2), J3.A7 (D-), J3.B7 (D-), U3.8 (UD-)
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
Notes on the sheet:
Pico 2 header: pin 1 = GP0 at the native-USB end; 2.54 mm pitch, 17.78 mm row spacing.
UART0: GP0 (TX, pin 1) -> CH343P RXD (pin 5); CH343P TXD (pin 4) -> GP1 (RX, pin 2).
PIO USB: GP12 (pin 16) = D+, GP13 (pin 17) = D-, 22 ohm series; HOST port (CC 56k Rp, VBUS from NATIVE USB).
Native USB: RP2350 USB_DP/USB_DM, 27 ohm series, USBLC6 ESD.
Power: NATIVE/UART VBUS are diode-ORed to VSYS; AP2112K-3.3 makes 3V3. PIO VBUS is an output from NATIVE VBUS.
BOOT: QSPI_SS --1k--> button --> GND. RUN: RUN --1k--> button --> GND.

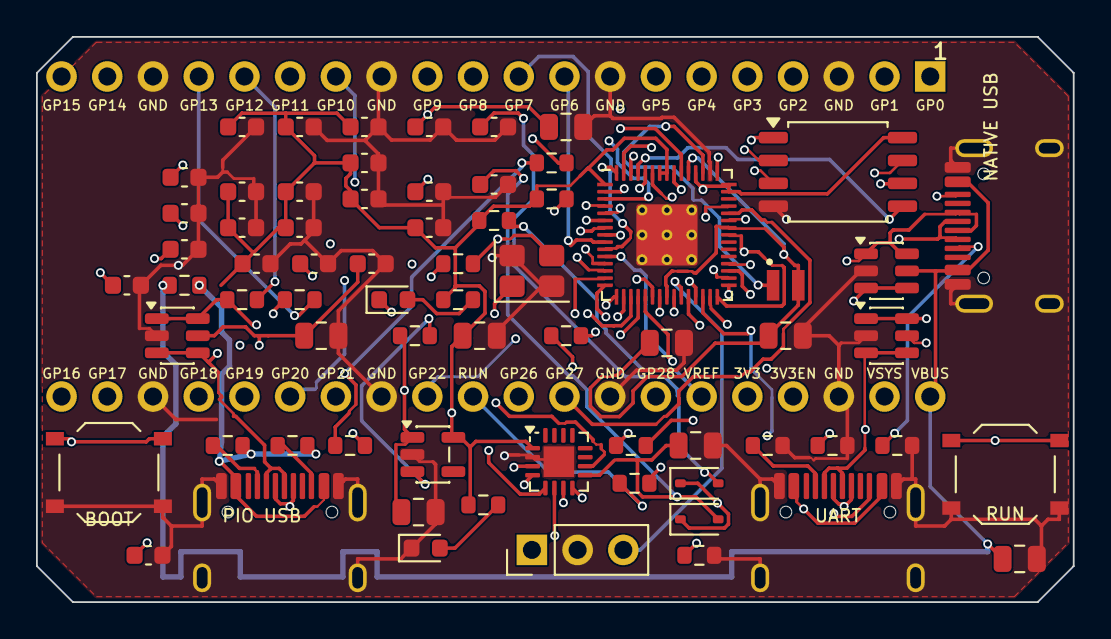
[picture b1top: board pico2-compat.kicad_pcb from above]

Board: 4 copper layers, 57.6 x 31.4 mm, 71 parts (0 on the bottom side), 70 nets.

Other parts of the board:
C30: 4.7uF; C_0805_2012Metric

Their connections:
1V1: C30.1; also elsewhere on the board
GND: C30.2; also elsewhere on the board

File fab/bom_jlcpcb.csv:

Comment,Designator,Footprint,LCSC Part #
RP2350A,U1,RP2350-QFN-60-1EP_7x7_P0.4mm_EP3.4x3.4mm_ThermalVias,C42411118
W25Q32JVSSIQ,U2,SOIC-8_5.3x5.3mm_P1.27mm,C179173
CH343P,U3,QFN-16-1EP_3x3mm_P0.5mm_EP1.7x1.7mm,C2846043
AP2112K-3.3,U4,SOT-23-5,C51118
TYPE-C-31-M-12,"J1,J2,J3",USB_C_Receptacle_HRO_TYPE-C-31-M-12,C165948
BAT54WS,"D1,D3",D_SOD-323,C22629
USBLC6-2SC6,"D4,D5,D6",SOT-23-6,C7519
5.1k,"R1,R2,R5,R6",R_0603_1608Metric,C23186
56k,"R3,R4",R_0603_1608Metric,C23206
27,"R7,R8",R_0603_1608Metric,C25190
22,"R9,R10",R_0603_1608Metric,C23345
0,"R11,R14",R_0603_1608Metric,C21189
1k,"R12,R13,R18,R19,R20",R_0603_1608Metric,C21190
33,R15,R_0603_1608Metric,C23140
200,R16,R_0603_1608Metric,C8218
100k,R17,R_0603_1608Metric,C14675
3.3uH,L1,L_pol_2016,C42411119
ABM8-272-T3,Y1,Crystal_SMD_3225-4Pin_3.2x2.5mm,C20625731
BOOT,SW1,SW_Push_1P1T_XKB_TS-1187A,C318884
RUN,SW2,SW_Push_1P1T_XKB_TS-1187A,C318884
KT-0603R,"LED1,LED2",LED_0603_1608Metric,C2286
10uF,"C1,C2,C3,C7,C9",C_0805_2012Metric,C15850
100nF,"C4,C5,C6,C8,C10,C12,C14,C15,C16,C17,C18,C19,C20,C21,C22,C23,C24,C27,C28,C29",C_0603_1608Metric,C14663
4.7uF,"C11,C13,C30",C_0805_2012Metric,C1779
15pF,"C25,C26",C_0603_1608Metric,C1644
